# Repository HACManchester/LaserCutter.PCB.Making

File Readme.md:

# Readme

A series of documentation / examples of making PCB's on the Orange Laser Cutter within the Manchester Hacspace

  * Documentation visible under http://HACManchester.github.io/LaserCutter.PCB.Making

All designs in here licensed under a Creative Commons Attribution-ShareAlike 4.0 International License.

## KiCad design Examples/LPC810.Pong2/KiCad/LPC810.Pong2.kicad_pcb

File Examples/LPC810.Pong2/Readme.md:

# Readme

Original schematic borrowed from <br>
https://github.com/Picatout/lpc810-pong/blob/master/ressource/Sch%C3%A9matique.pdf

This is just an updated schemtaic for the latest version of KiCad
It's a small circuit that allows the playing of Pong on an LPC810

This was originally licenced under the GPL 3.0, so this should be the same

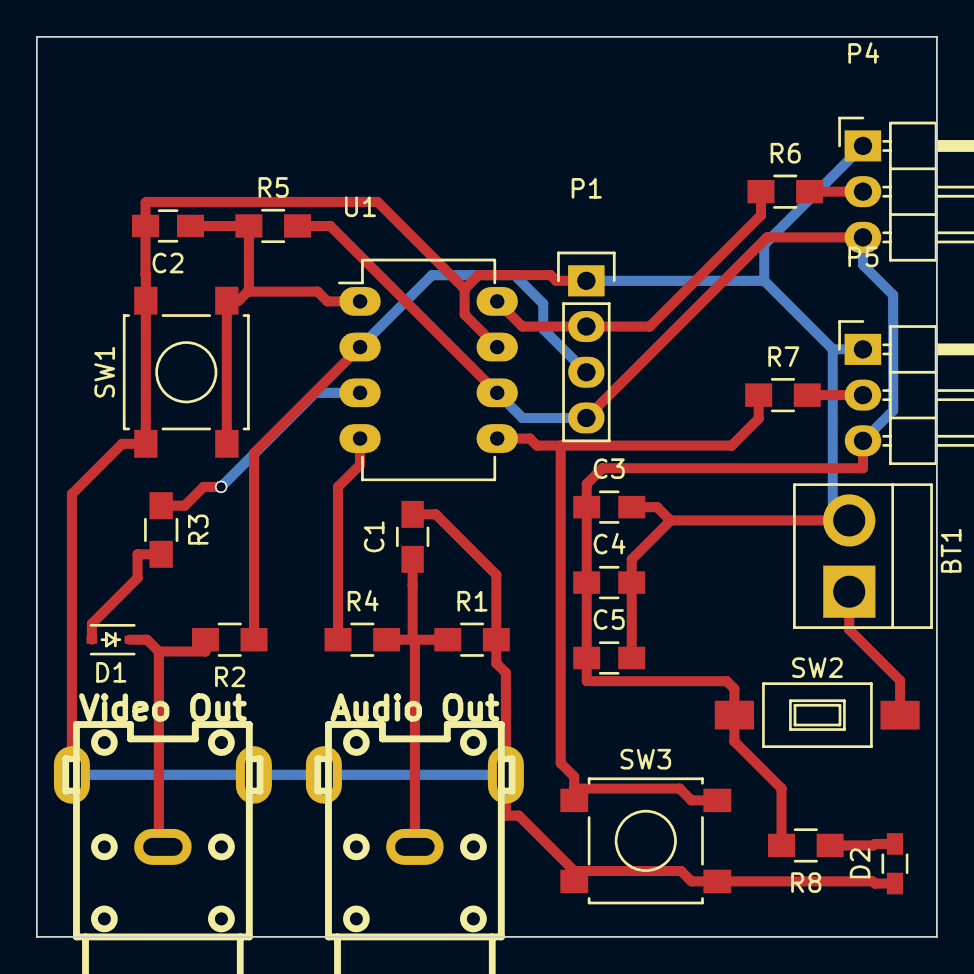
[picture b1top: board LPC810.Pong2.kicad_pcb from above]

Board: 2 copper layers, 50.0 x 50.0 mm, 25 parts (0 on the bottom side), 15 nets.

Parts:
BT1: Battery; Pin_Header_Straight_1x02_Pitch3.96mm_Friction_Lock
C1: 2.2n; C_0805_HandSoldering
C2, C3, C4, C5: 100n; C_0805_HandSoldering
D1: BAS70JFILM; SOD-323
D2: PWR LED; R_0603_HandSoldering
P1: Serial Prog; Pin_Header_Straight_1x04
P2: Video Out; rca_yellow
P3: Audio Out; rca_yellow
P4: Paddle 1; Pin_Header_Angled_1x03
P5: Paddle 2; Pin_Header_Angled_1x03
R1: 620R; R_0805_HandSoldering
R2: 680R; R_0805_HandSoldering
R3, R8: 120R; R_0805_HandSoldering
R4, R5: 10K; R_0805_HandSoldering
R6, R7: 1K; R_0805_HandSoldering
SW1: ~Reset; SW_SPST_B3S-1000
SW2: Power; SW_SPST_FSMSM
SW3: Program; SW_SPST_B3S-1000
U1: LPC810M021FN8; DIP-8_W7.62mm_LongPads

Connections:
/DAUDIO: R4.1, U1.4
/DSYNC: P1.3, R2.1, U1.2
/DVIDEO: R3.1, U1.3
/P1: P1.2, R6.1, U1.8
/P2: R7.1, SW3.1, U1.5
GND: BT1.2, C1.2, C2.2, C3.2, C4.2, C5.2, D2.1, P1.1, P2.2, P3.2, P4.1, P5.1, R1.2, SW1.1, SW3.2, U1.7
unnamed: BT1.1, SW2.2
unnamed: C1.1, P3.1, R1.1, R4.2
unnamed: C2.1, R5.1, SW1.2, U1.1
unnamed: D1.1, P2.1, R2.2
unnamed: D1.2, R3.2
unnamed: D2.2, R8.1
unnamed: P4.2, R6.2
unnamed: P5.2, R7.2
VDD: C3.1, C4.1, C5.1, P1.4, P4.3, P5.3, R5.2, R8.2, SW2.1, U1.6

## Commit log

2016-04-01 Deployed fa3e048 with MkDocs version: 0.15.3
2016-04-04 added lpc810 pong board to examples
2016-04-06 Deployed 64aec42 with MkDocs version: 0.15.3
2016-04-06 Added more docs for KiCad
2016-04-08 Re-arrange docs for KiCad
2016-04-08 Deployed bda186b with MkDocs version: 0.15.3
